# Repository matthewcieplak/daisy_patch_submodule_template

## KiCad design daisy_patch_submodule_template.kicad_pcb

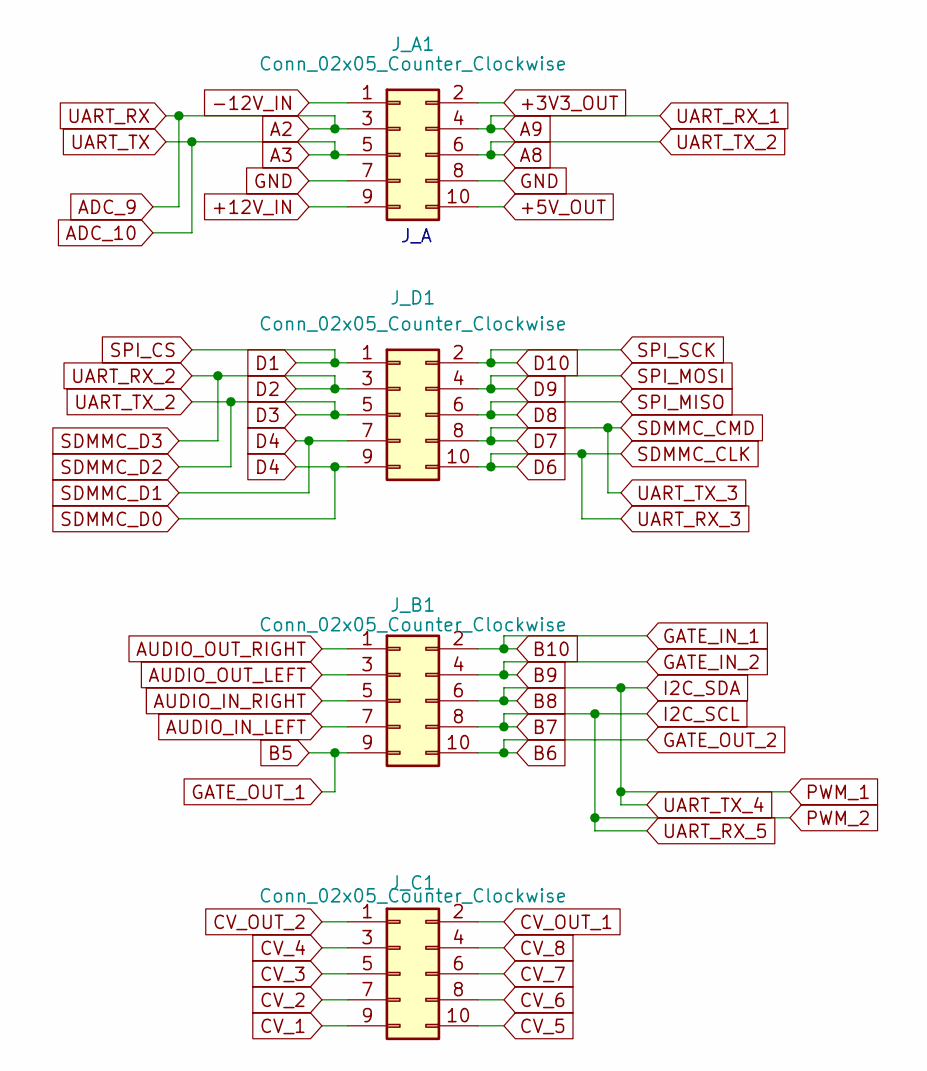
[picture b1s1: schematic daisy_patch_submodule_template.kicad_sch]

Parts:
J_A1: Conn_02x05_Counter_Clockwise; PinHeader_2x05_P2.54mm_Vertical
J_B1: Conn_02x05_Counter_Clockwise; PinHeader_2x05_P2.54mm_Vertical
J_C1: Conn_02x05_Counter_Clockwise; PinHeader_2x05_P2.54mm_Vertical
J_D1: Conn_02x05_Counter_Clockwise; PinHeader_2x05_P2.54mm_Vertical

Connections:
+3V3_OUT: J_A1.2
+5V_OUT: J_A1.10
+12V_IN: J_A1.9
-12V_IN: J_A1.1
A2: J_A1.3
A3: J_A1.5
A8: J_A1.6, J_D1.5
A9: J_A1.4
AUDIO_IN_LEFT: J_B1.7
AUDIO_IN_RIGHT: J_B1.5
AUDIO_OUT_LEFT: J_B1.3
AUDIO_OUT_RIGHT: J_B1.1
B5: J_B1.9
B6: J_B1.10
B7: J_B1.8
B8: J_B1.6
B9: J_B1.4
B10: J_B1.2
CV_1: J_C1.9
CV_2: J_C1.7
CV_3: J_C1.5
CV_4: J_C1.3
CV_5: J_C1.10
CV_6: J_C1.8
CV_7: J_C1.6
CV_8: J_C1.4
CV_OUT_1: J_C1.2
CV_OUT_2: J_C1.1
D1: J_D1.1
D2: J_D1.3
D4: J_D1.7, J_D1.9
D6: J_D1.10
D7: J_D1.8
D8: J_D1.6
D9: J_D1.4
D10: J_D1.2
GND: J_A1.7, J_A1.8

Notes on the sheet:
J_A

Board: 2 copper layers, 4 parts (0 on the bottom side), 3 nets, no tracks yet.

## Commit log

2023-07-03 Standard kicad gitignore
2023-07-03 Adding patch datasheet
